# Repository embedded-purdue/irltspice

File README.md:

# IRLTSPICE - An ES@P Project

IRL + LTspice = IRLTSPICE!

IRLTSPICE provides the convenience of spice with the accuracy and testability of a real-life analog circuit.

Simply design your circuit in your EDA tool of choice, or use our handy Python API, upload to the board, and bang!
Your circuit now exists in real life, and you can now do whatever you want!

Run FRAs, send audio through it, use it as a testbed, or whatever else you can imagine.
It's now just an analog circuit.

Analog protyping has never been this easy.

## How it works

The IRLTSPICE board features a bank of resistors, capacitors, and op-amps, so every virtual component has a physical counterpart that was already on the board.

These physical components are then connected to each other via specialized switches, such that the nets are the same as in your virtual design.

## About

IRLTSPICE began as a Purdue Electrical and Computer Engineering senior design project, and is now an Embedded Systems at Purdue (ES@P) project.

## Project Structure
The senior design project uses a monorepo architecture with the following sub-directories:
- `hardware/` Hardware schematics
- `firmware/` Microcontroller firmware
- `software/` On-PC software
- `evilware/` Evil Circuits and Code

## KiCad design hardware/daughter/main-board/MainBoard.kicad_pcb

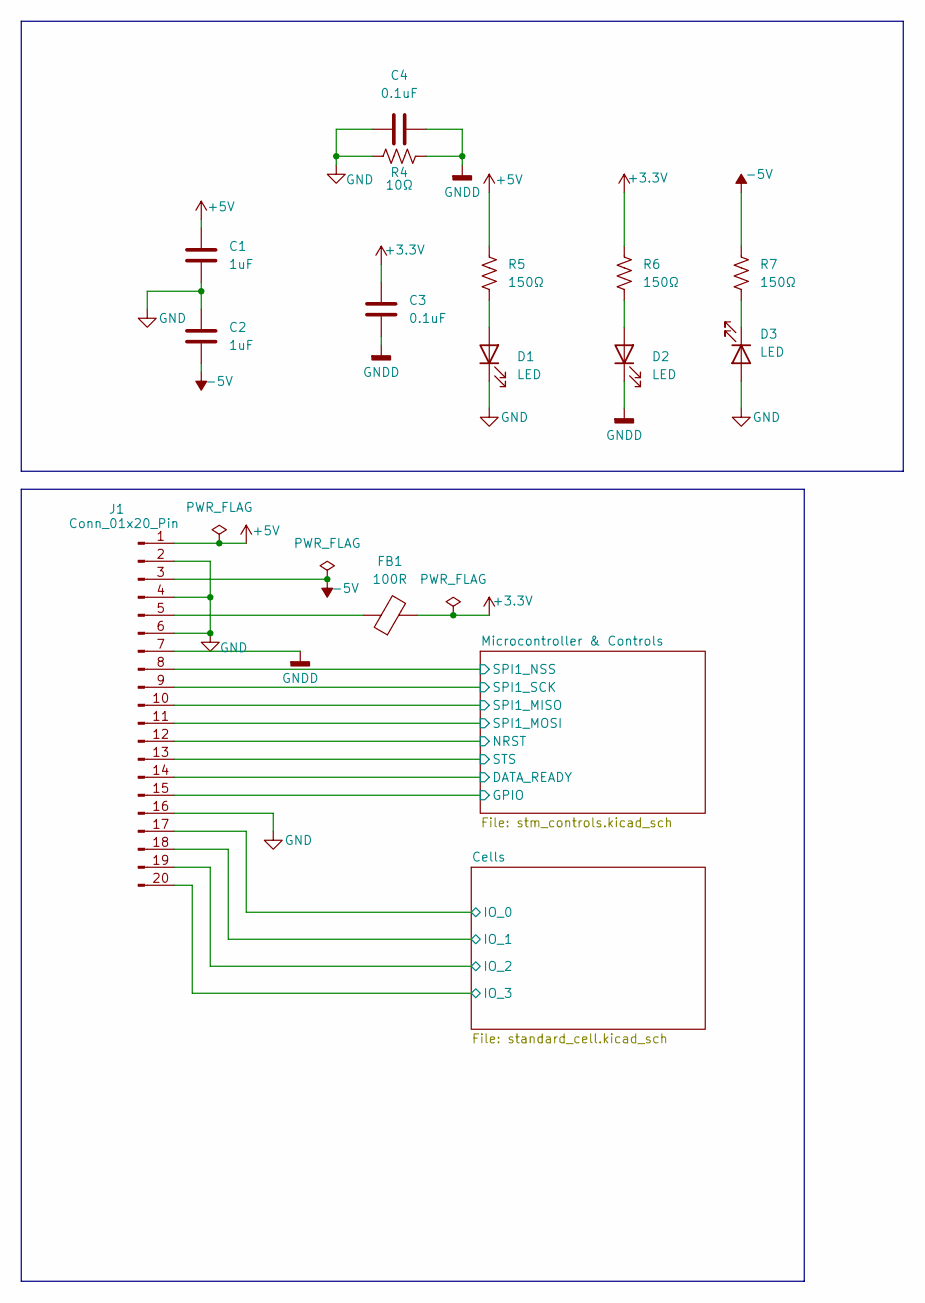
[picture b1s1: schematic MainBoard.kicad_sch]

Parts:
C1, C2: 1uF; C_0603_1608Metric_Pad1.08x0.95mm_HandSolder
C3, C4: 0.1uF; C_0603_1608Metric_Pad1.08x0.95mm_HandSolder
D1, D2, D3: LED; D_0805_2012Metric_Pad1.15x1.40mm_HandSolder
FB1: 100R; R_0603_1608Metric_Pad0.98x0.95mm_HandSolder
J1: Conn_01x20_Pin; PinHeader_2x10_P2.54mm_Horizontal
R4: 10Ω; R_0805_2012Metric_Pad1.20x1.40mm_HandSolder
R5, R6, R7: 150Ω; R_0603_1608Metric_Pad0.98x0.95mm_HandSolder

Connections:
+3.3V: C3.2, FB1.2, R6.1; also elsewhere on the board
+5V: C1.2, J1.1, R5.1; also elsewhere on the board
-5V: C2.1, J1.3, R7.1; also elsewhere on the board
/Cells/IO_0: J1.17; also elsewhere on the board
/Cells/IO_1: J1.18; also elsewhere on the board
/Cells/IO_2: J1.19; also elsewhere on the board
/Cells/IO_3: J1.20; also elsewhere on the board
/Microcontroller & Controls/DATA_READY: J1.14; also elsewhere on the board
/Microcontroller & Controls/GPIO: J1.15; also elsewhere on the board
/Microcontroller & Controls/NRST: J1.12; also elsewhere on the board
/Microcontroller & Controls/SPI1_MISO: J1.10; also elsewhere on the board
/Microcontroller & Controls/SPI1_MOSI: J1.11; also elsewhere on the board
/Microcontroller & Controls/SPI1_NSS: J1.8; also elsewhere on the board
/Microcontroller & Controls/SPI1_SCK: J1.9; also elsewhere on the board
/Microcontroller & Controls/STS: J1.13; also elsewhere on the board
GND: C1.1, C2.2, C4.1, D1.1 (K), D3.2 (A), J1.2, J1.4, J1.6, J1.16, R4.1; also elsewhere on the board
GNDD: C3.1, C4.2, D2.1 (K), J1.7, R4.2; also elsewhere on the board
unnamed: D1.2 (A), R5.2
unnamed: D2.2 (A), R6.2
unnamed: D3.1 (K), R7.2
unnamed: FB1.1, J1.5

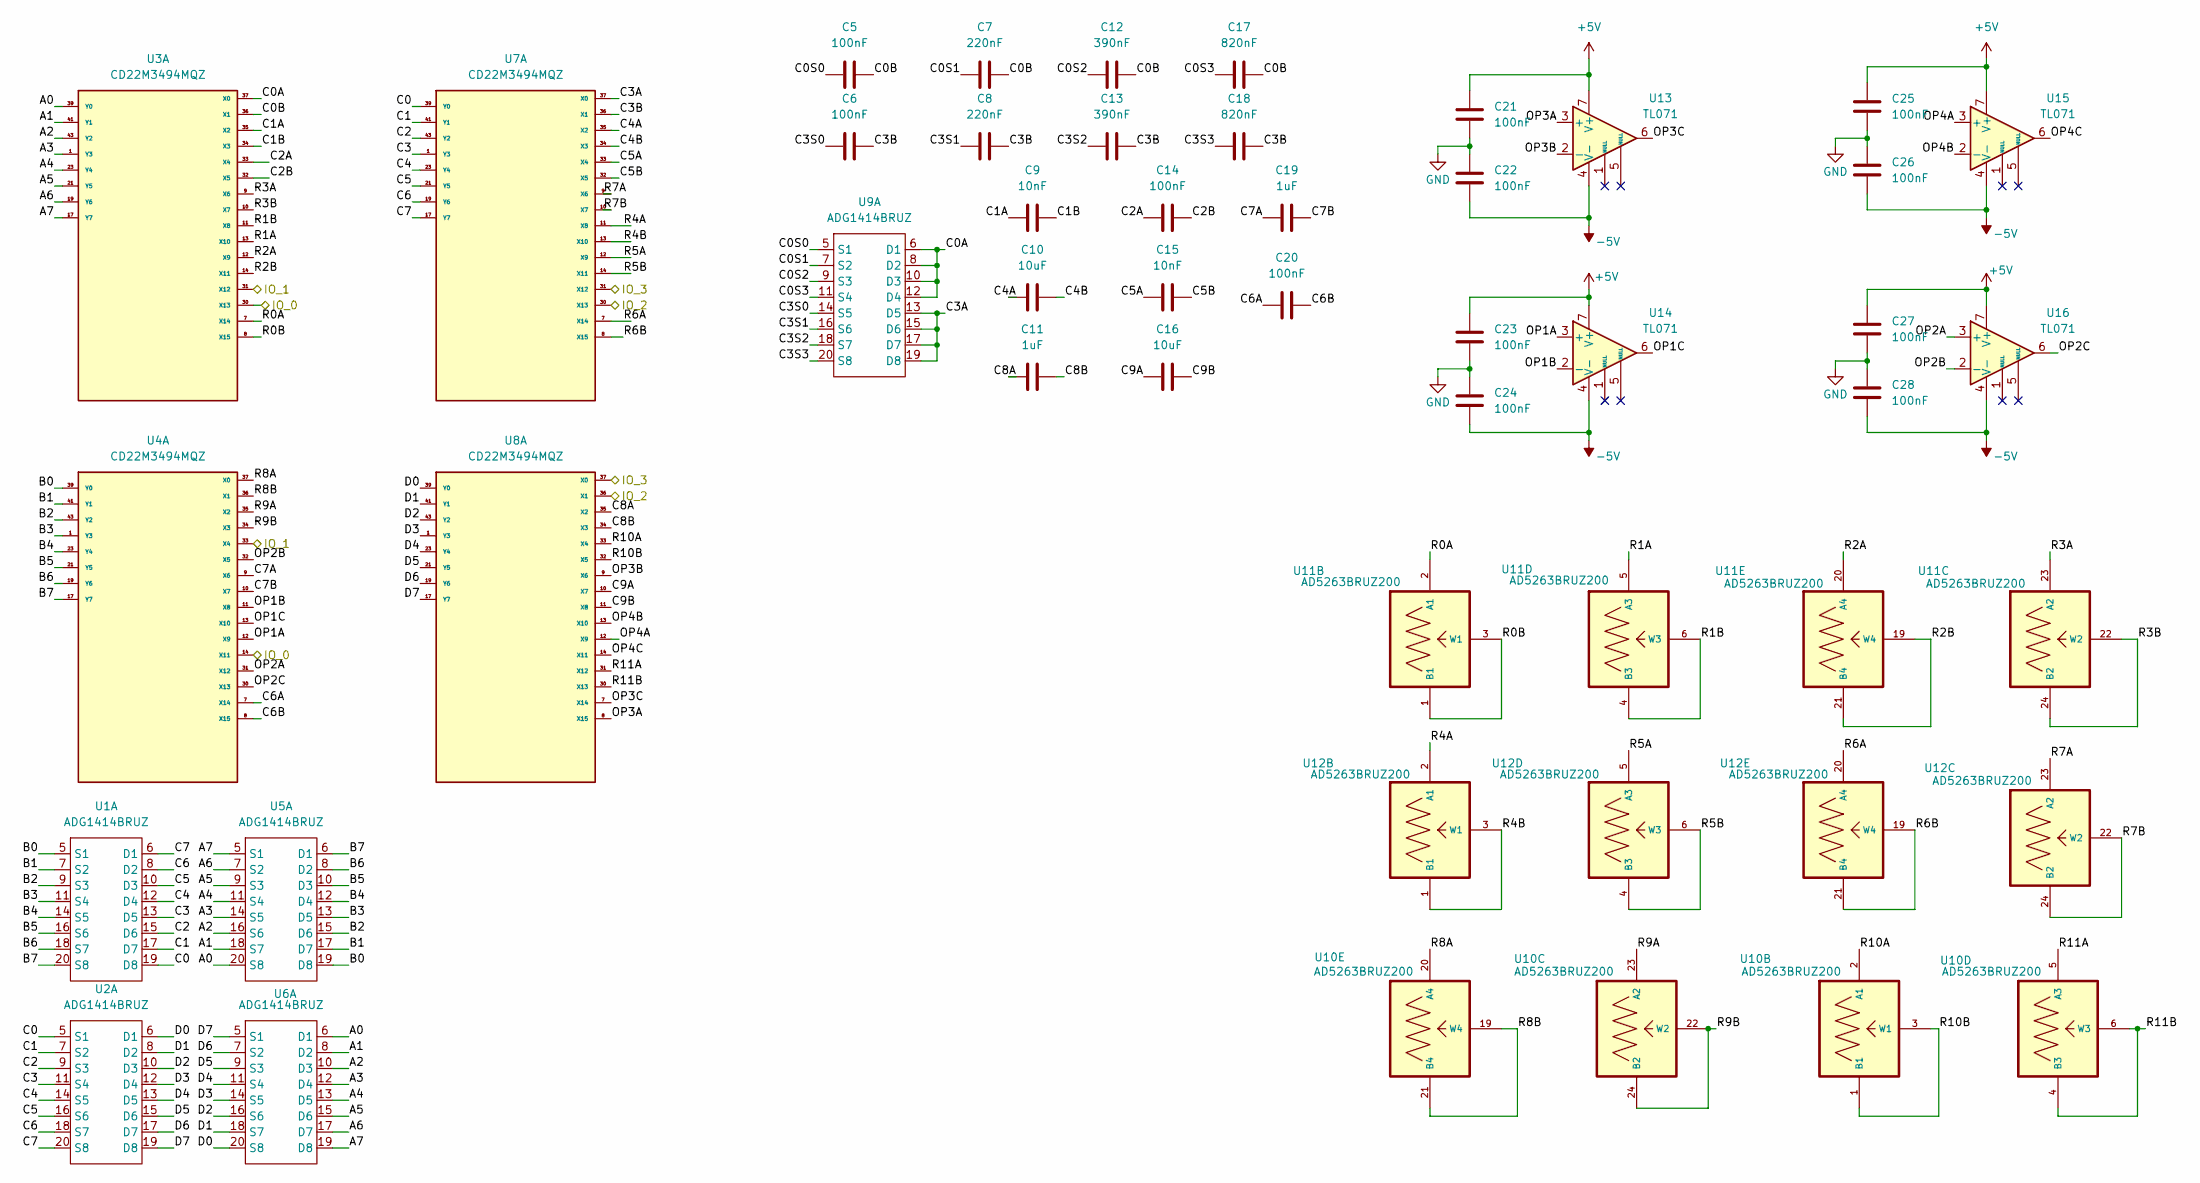
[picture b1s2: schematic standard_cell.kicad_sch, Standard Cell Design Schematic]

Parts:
C5, C6, C14, C20, C21, C22, C23, C24, C25, C26, C27, C28: 100nF; C_0603_1608Metric_Pad1.08x0.95mm_HandSolder
C7, C8: 220nF; C_0603_1608Metric_Pad1.08x0.95mm_HandSolder
C9, C15: 10nF; C_0603_1608Metric_Pad1.08x0.95mm_HandSolder
C10, C16: 10uF; C_0805_2012Metric_Pad1.18x1.45mm_HandSolder
C11, C19: 1uF; C_0603_1608Metric_Pad1.08x0.95mm_HandSolder
C12, C13: 390nF; C_0603_1608Metric_Pad1.08x0.95mm_HandSolder
C17, C18: 820nF; C_0603_1608Metric_Pad1.08x0.95mm_HandSolder
U1, U2, U5, U6, U9: ADG1414BRUZ; HTSSOP-24-1EP_4.4x7.8mm_P0.65mm_EP3.2x5mm
U3, U4, U7, U8: CD22M3494MQZ; PLCC44_16P66X16P66_INR-M; PARTREV September 2011
U10, U11, U12: AD5263BRUZ200; SOP65P640X120-24N; MPN AD5263BRUZ200
U13, U14, U15, U16: TL071; SOIC-8-1EP_3.9x4.9mm_P1.27mm_EP2.29x3mm

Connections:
+5V: C21.1, C23.1, C25.1, C27.1, U13.7 (V+), U14.7 (V+), U15.7 (V+), U16.7 (V+); also elsewhere on the board
-5V: C22.2, C24.2, C26.2, C28.2, U13.4 (V-), U14.4 (V-), U15.4 (V-), U16.4 (V-); also elsewhere on the board
/Cells/A0: U3.39 (Y0), U5.20 (S8), U6.6 (D1)
/Cells/A1: U3.41 (Y1), U5.18 (S7), U6.8 (D2)
/Cells/A2: U3.43 (Y2), U5.16 (S6), U6.10 (D3)
/Cells/A3: U3.1 (Y3), U5.14 (S5), U6.12 (D4)
/Cells/A4: U3.23 (Y4), U5.11 (S4), U6.13 (D5)
/Cells/A5: U3.21 (Y5), U5.9 (S3), U6.15 (D6)
/Cells/A6: U3.19 (Y6), U5.7 (S2), U6.17 (D7)
/Cells/A7: U3.17 (Y7), U5.5 (S1), U6.19 (D8)
/Cells/B0: U1.5 (S1), U4.39 (Y0), U5.19 (D8)
/Cells/B1: U1.7 (S2), U4.41 (Y1), U5.17 (D7)
/Cells/B2: U1.9 (S3), U4.43 (Y2), U5.15 (D6)
/Cells/B3: U1.11 (S4), U4.1 (Y3), U5.13 (D5)
/Cells/B4: U1.14 (S5), U4.23 (Y4), U5.12 (D4)
/Cells/B5: U1.16 (S6), U4.21 (Y5), U5.10 (D3)
/Cells/B6: U1.18 (S7), U4.19 (Y6), U5.8 (D2)
/Cells/B7: U1.20 (S8), U4.17 (Y7), U5.6 (D1)
/Cells/C0: U1.19 (D8), U2.5 (S1), U7.39 (Y0)
/Cells/C0A: U3.37 (X0), U9.6 (D1), U9.8 (D2), U9.10 (D3), U9.12 (D4)
/Cells/C0B: C5.2, C7.2, C12.2, C17.2, U3.36 (X1)
/Cells/C0S0: C5.1, U9.5 (S1)
/Cells/C0S1: C7.1, U9.7 (S2)
/Cells/C0S2: C12.1, U9.9 (S3)
/Cells/C0S3: C17.1, U9.11 (S4)
/Cells/C1: U1.17 (D7), U2.7 (S2), U7.41 (Y1)
/Cells/C1A: C9.1, U3.35 (X2)
/Cells/C1B: C9.2, U3.34 (X3)
/Cells/C2: U1.15 (D6), U2.9 (S3), U7.43 (Y2)
/Cells/C2A: C14.1, U3.33 (X4)
/Cells/C2B: C14.2, U3.32 (X5)
/Cells/C3: U1.13 (D5), U2.11 (S4), U7.1 (Y3)
/Cells/C3A: U7.37 (X0), U9.13 (D5), U9.15 (D6), U9.17 (D7), U9.19 (D8)
/Cells/C3B: C6.2, C8.2, C13.2, C18.2, U7.36 (X1)
/Cells/C3S0: C6.1, U9.14 (S5)
/Cells/C3S1: C8.1, U9.16 (S6)
/Cells/C3S2: C13.1, U9.18 (S7)
/Cells/C3S3: C18.1, U9.20 (S8)
/Cells/C4: U1.12 (D4), U2.14 (S5), U7.23 (Y4)
/Cells/C4A: C10.1, U7.35 (X2)
/Cells/C4B: C10.2, U7.34 (X3)
/Cells/C5: U1.10 (D3), U2.16 (S6), U7.21 (Y5)
/Cells/C5A: C15.1, U7.33 (X4)
/Cells/C5B: C15.2, U7.32 (X5)
/Cells/C6: U1.8 (D2), U2.18 (S7), U7.19 (Y6)
/Cells/C6A: C20.1, U4.7 (X14)
/Cells/C6B: C20.2, U4.8 (X15)
/Cells/C7: U1.6 (D1), U2.20 (S8), U7.17 (Y7)
/Cells/C7A: C19.1, U4.9 (X6)
/Cells/C7B: C19.2, U4.10 (X7)
/Cells/C8A: C11.1, U8.35 (X2)
/Cells/C8B: C11.2, U8.34 (X3)
/Cells/C9A: C16.1, U8.10 (X7)
/Cells/C9B: C16.2, U8.11 (X8)
/Cells/D0: U2.6 (D1), U6.20 (S8), U8.39 (Y0)
/Cells/D1: U2.8 (D2), U6.18 (S7), U8.41 (Y1)
/Cells/D2: U2.10 (D3), U6.16 (S6), U8.43 (Y2)
/Cells/D3: U2.12 (D4), U6.14 (S5), U8.1 (Y3)
/Cells/D4: U2.13 (D5), U6.11 (S4), U8.23 (Y4)
/Cells/D5: U2.15 (D6), U6.9 (S3), U8.21 (Y5)
/Cells/D6: U2.17 (D7), U6.7 (S2), U8.19 (Y6)
/Cells/D7: U2.19 (D8), U6.5 (S1), U8.17 (Y7)
/Cells/IO_0: U3.30 (X13), U4.14 (X11); also elsewhere on the board
/Cells/IO_1: U3.31 (X12), U4.33 (X4); also elsewhere on the board
/Cells/IO_2: U7.30 (X13), U8.36 (X1); also elsewhere on the board
/Cells/IO_3: U7.31 (X12), U8.37 (X0); also elsewhere on the board
/Cells/OP1A: U4.12 (X9), U14.3 (+)
/Cells/OP1B: U4.11 (X8), U14.2 (-)
/Cells/OP1C: U4.13 (X10), U14.6
/Cells/OP2A: U4.31 (X12), U16.3 (+)
/Cells/OP2B: U4.32 (X5), U16.2 (-)
/Cells/OP2C: U4.30 (X13), U16.6
/Cells/OP3A: U8.8 (X15), U13.3 (+)
/Cells/OP3B: U8.9 (X6), U13.2 (-)
/Cells/OP3C: U8.7 (X14), U13.6
/Cells/OP4A: U8.12 (X9), U15.3 (+)
/Cells/OP4B: U8.13 (X10), U15.2 (-)
/Cells/OP4C: U8.14 (X11), U15.6
/Cells/R0A: U3.7 (X14), U11.2 (A1)
/Cells/R0B: U3.8 (X15), U11.1 (B1), U11.3 (W1)
/Cells/R1A: U3.13 (X10), U11.5 (A3)
/Cells/R1B: U3.11 (X8), U11.4 (B3), U11.6 (W3)
/Cells/R2A: U3.12 (X9), U11.20 (A4)
/Cells/R2B: U3.14 (X11), U11.19 (W4), U11.21 (B4)
/Cells/R3A: U3.9 (X6), U11.23 (A2)
/Cells/R3B: U3.10 (X7), U11.22 (W2), U11.24 (B2)
/Cells/R4A: U7.11 (X8), U12.2 (A1)
/Cells/R4B: U7.13 (X10), U12.1 (B1), U12.3 (W1)
/Cells/R5A: U7.12 (X9), U12.5 (A3)
/Cells/R5B: U7.14 (X11), U12.4 (B3), U12.6 (W3)
/Cells/R6A: U7.7 (X14), U12.20 (A4)
/Cells/R6B: U7.8 (X15), U12.19 (W4), U12.21 (B4)
/Cells/R7A: U7.9 (X6), U12.23 (A2)
/Cells/R7B: U7.10 (X7), U12.22 (W2), U12.24 (B2)
/Cells/R8A: U4.37 (X0), U10.20 (A4)
/Cells/R8B: U4.36 (X1), U10.19 (W4), U10.21 (B4)
/Cells/R9A: U4.35 (X2), U10.23 (A2)
/Cells/R9B: U4.34 (X3), U10.22 (W2), U10.24 (B2)
/Cells/R10A: U8.33 (X4), U10.2 (A1)
/Cells/R10B: U8.32 (X5), U10.1 (B1), U10.3 (W1)
/Cells/R11A: U8.31 (X12), U10.5 (A3)
/Cells/R11B: U8.30 (X13), U10.4 (B3), U10.6 (W3)
GND: C21.2, C22.1, C23.2, C24.1, C25.2, C26.1, C27.2, C28.1; also elsewhere on the board

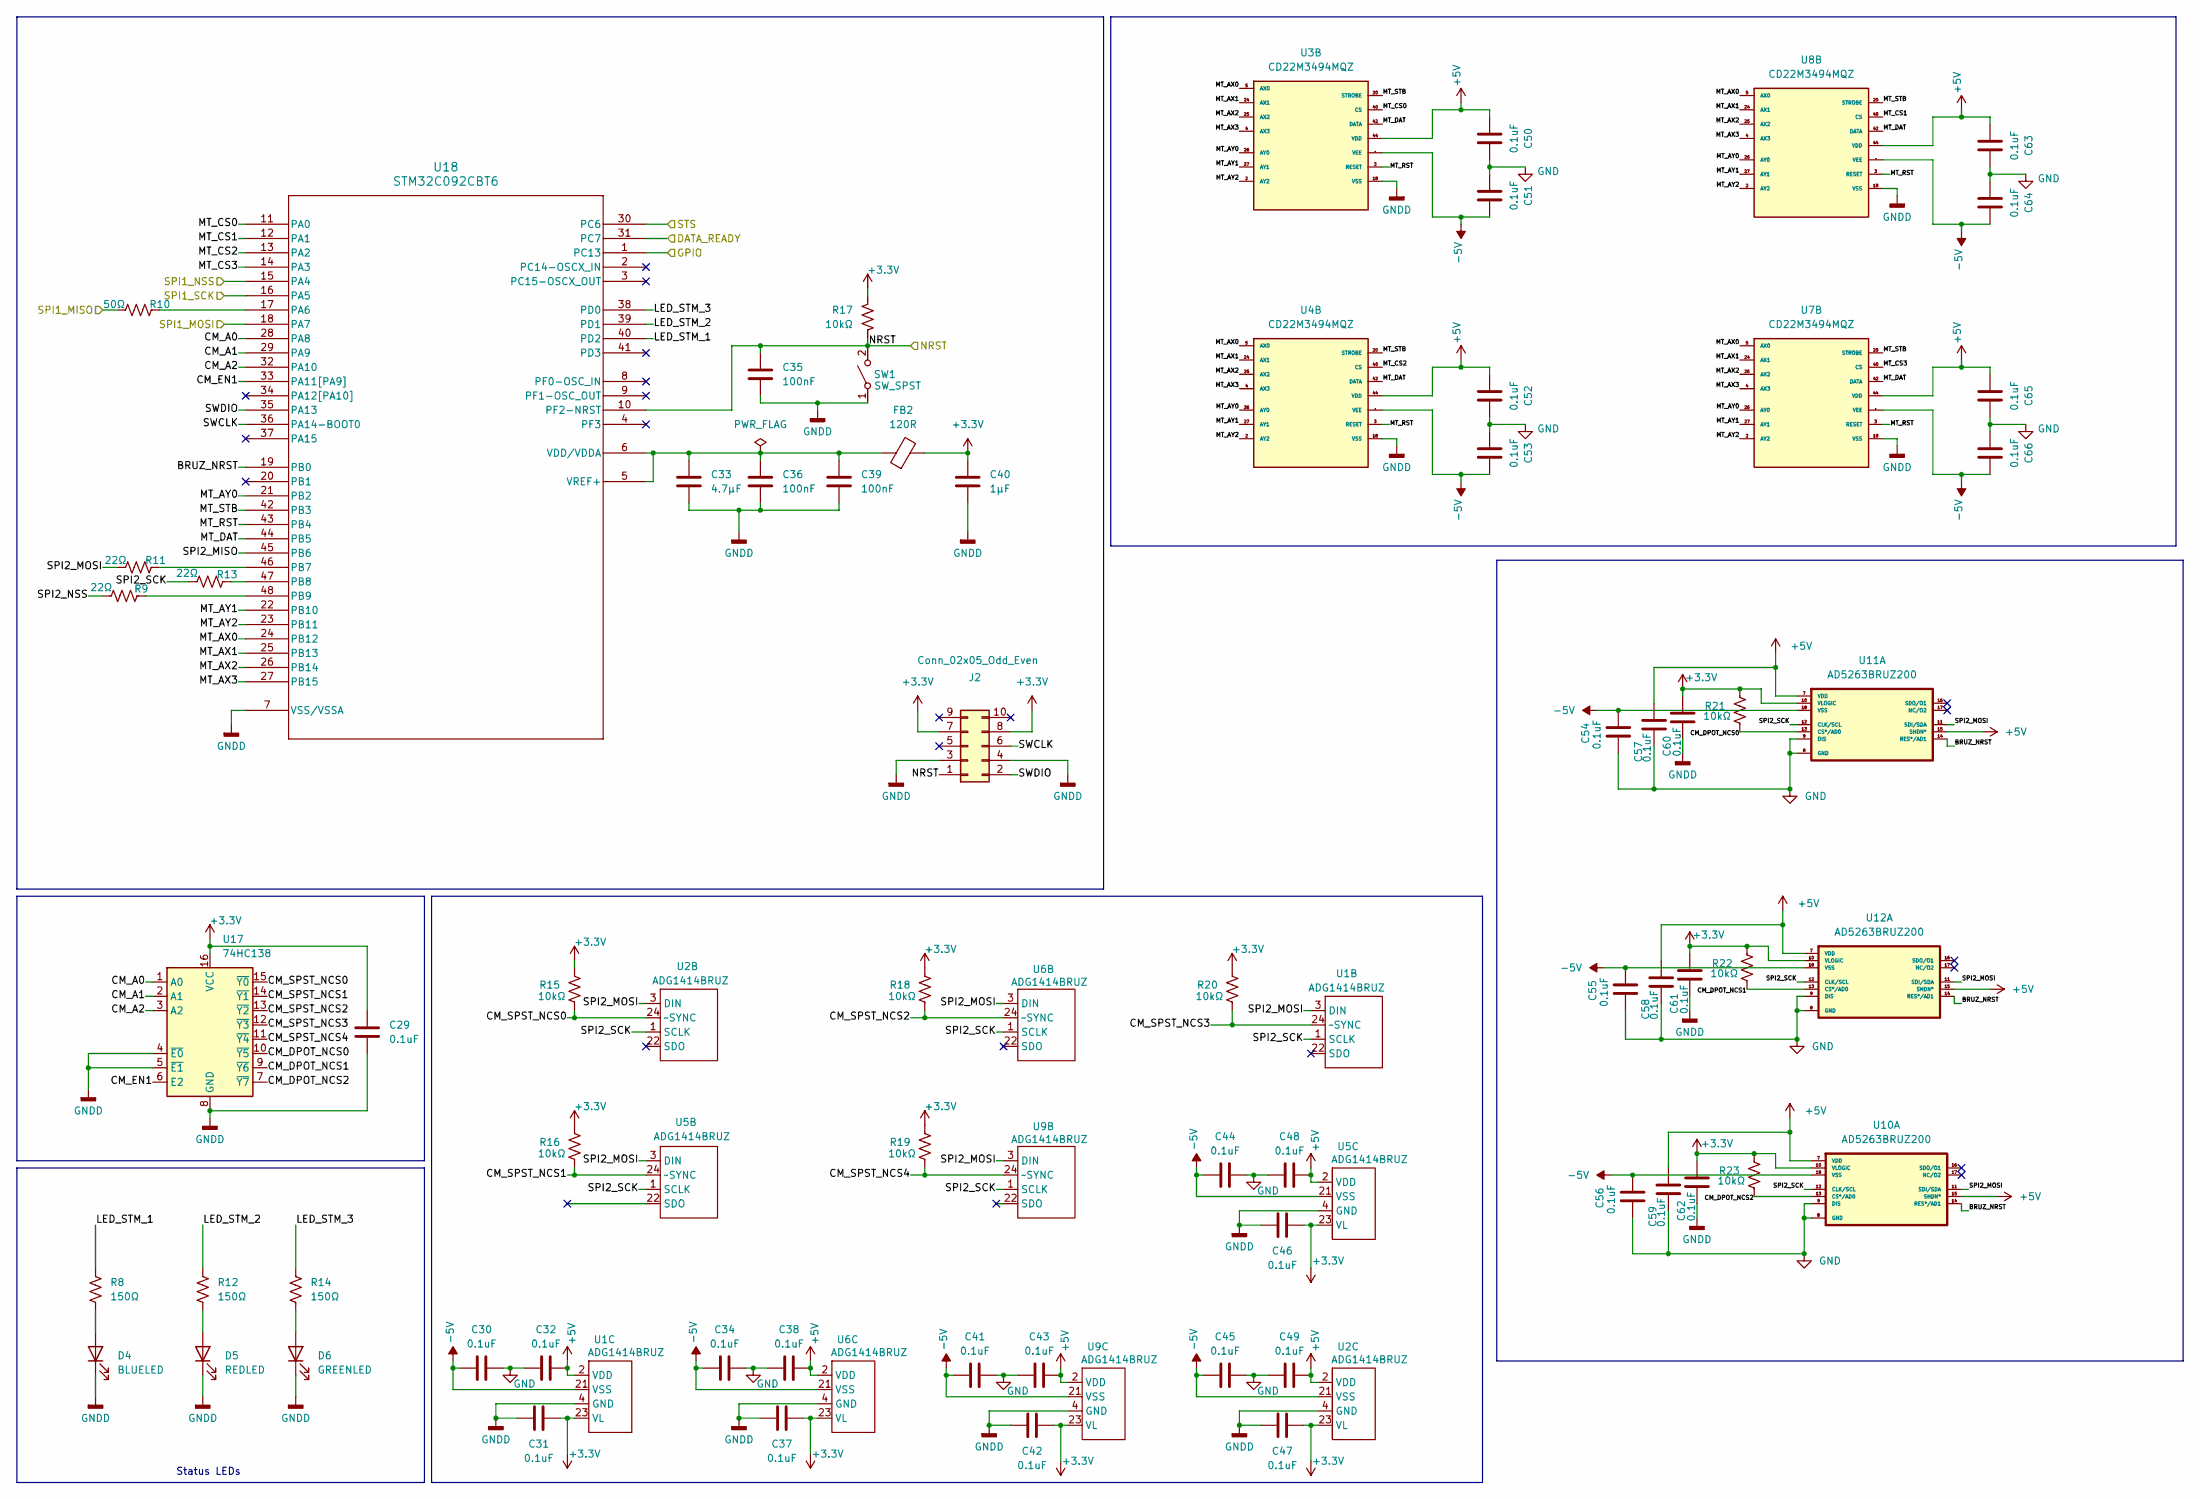
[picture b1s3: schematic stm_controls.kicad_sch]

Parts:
C29, C30, C31, C32, C34, C37, C38, C41, C42, C43, C44, C45, C46, C47, C48, C49, C50, C51, C52, C53, C54, C55, C56, C57, C58, C59, C60, C61, C62, C63, C64, C65, C66: 0.1uF; C_0603_1608Metric_Pad1.08x0.95mm_HandSolder
C33: 4.7µF; C_0603_1608Metric_Pad1.08x0.95mm_HandSolder
C35, C36, C39: 100nF; C_0603_1608Metric_Pad1.08x0.95mm_HandSolder
C40: 1µF; C_0603_1608Metric_Pad1.08x0.95mm_HandSolder
D4: BLUELED; D_0805_2012Metric_Pad1.15x1.40mm_HandSolder
D5: REDLED; D_0805_2012Metric_Pad1.15x1.40mm_HandSolder
D6: GREENLED; D_0805_2012Metric_Pad1.15x1.40mm_HandSolder
FB2: 120R; L_0603_1608Metric_Pad1.05x0.95mm_HandSolder
J2: Conn_02x05_Odd_Even; PinHeader_2x05_P2.54mm_Vertical
R8, R12, R14: 150Ω; R_0603_1608Metric_Pad0.98x0.95mm_HandSolder
R9, R11, R13: 22Ω; R_0603_1608Metric_Pad0.98x0.95mm_HandSolder
R10: 50Ω; R_0603_1608Metric_Pad0.98x0.95mm_HandSolder
R15, R16, R17, R18, R19, R20, R21, R22, R23: 10kΩ; R_0603_1608Metric_Pad0.98x0.95mm_HandSolder
SW1: SW_SPST; SW_SPST_SKQG_WithoutStem
U1, U2, U5, U6, U9: ADG1414BRUZ; HTSSOP-24-1EP_4.4x7.8mm_P0.65mm_EP3.2x5mm
U3, U4, U7, U8: CD22M3494MQZ; PLCC44_16P66X16P66_INR-M; PARTREV September 2011
U10, U11, U12: AD5263BRUZ200; SOP65P640X120-24N
U17: 74HC138; SOIC-16_3.9x9.9mm_P1.27mm
U18: STM32C092CBT6; LQFP48_STM

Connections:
+3.3V: C29.1, C31.1, C37.1, C40.1, C42.1, C46.1, C47.1, C60.1, C61.1, C62.1, FB2.2, J2.7, J2.8, R15.2, R16.2, R17.1, R18.2, R19.2, R20.2, R21.2, R22.2, R23.2, U1.23 (VL), U2.23 (VL), U5.23 (VL), U6.23 (VL), U9.23 (VL), U10.10 (VLOGIC), U11.10 (VLOGIC), U12.10 (VLOGIC), U17.16 (VCC); also elsewhere on the board
+5V: C32.1, C38.1, C43.1, C48.1, C49.1, C50.1, C52.1, C57.1, C58.1, C59.1, C63.1, C65.1, U1.2 (VDD), U2.2 (VDD), U3.44 (VDD), U4.44 (VDD), U5.2 (VDD), U6.2 (VDD), U7.44 (VDD), U8.44 (VDD), U9.2 (VDD), U10.7 (VDD), U10.15 (SHDN*), U11.7 (VDD), U11.15 (SHDN*), U12.7 (VDD), U12.15 (SHDN*); also elsewhere on the board
-5V: C30.2, C34.2, C41.2, C44.2, C45.2, C51.2, C53.2, C54.1, C55.1, C56.1, C64.2, C66.2, U1.21 (VSS), U2.21 (VSS), U3.22 (VEE), U4.22 (VEE), U5.21 (VSS), U6.21 (VSS), U7.22 (VEE), U8.22 (VEE), U9.21 (VSS), U10.18 (VSS), U11.18 (VSS), U12.18 (VSS); also elsewhere on the board
/Microcontroller & Controls/BRUZ_NRST: U10.14 (RES*/AD1), U11.14 (RES*/AD1), U12.14 (RES*/AD1), U18.19 (PB0)
/Microcontroller & Controls/CM_A0: U17.1 (A0), U18.28 (PA8)
/Microcontroller & Controls/CM_A1: U17.2 (A1), U18.29 (PA9)
/Microcontroller & Controls/CM_A2: U17.3 (A2), U18.32 (PA10)
/Microcontroller & Controls/CM_DPOT_NCS0: R21.1, U11.13 (CS*/AD0), U17.10 (~Y5)
/Microcontroller & Controls/CM_DPOT_NCS1: R22.1, U12.13 (CS*/AD0), U17.9 (~Y6)
/Microcontroller & Controls/CM_DPOT_NCS2: R23.1, U10.13 (CS*/AD0), U17.7 (~Y7)
/Microcontroller & Controls/CM_EN1: U17.6 (E2), U18.33 (PA11[PA9])
/Microcontroller & Controls/CM_SPST_NCS0: R15.1, U2.24 (~SYNC), U17.15 (~Y0)
/Microcontroller & Controls/CM_SPST_NCS1: R16.1, U5.24 (~SYNC), U17.14 (~Y1)
/Microcontroller & Controls/CM_SPST_NCS2: R18.1, U6.24 (~SYNC), U17.13 (~Y2)
/Microcontroller & Controls/CM_SPST_NCS3: R20.1, U1.24 (~SYNC), U17.12 (~Y3)
/Microcontroller & Controls/CM_SPST_NCS4: R19.1, U9.24 (~SYNC), U17.11 (~Y4)
/Microcontroller & Controls/DATA_READY: U18.31 (PC7); also elsewhere on the board
/Microcontroller & Controls/GPIO: U18.1 (PC13); also elsewhere on the board
/Microcontroller & Controls/LED_STM_1: R8.1, U18.40 (PD2)
/Microcontroller & Controls/LED_STM_2: R12.1, U18.39 (PD1)
/Microcontroller & Controls/LED_STM_3: R14.1, U18.38 (PD0)
/Microcontroller & Controls/MT_AX0: U3.5 (AX0), U4.5 (AX0), U7.5 (AX0), U8.5 (AX0), U18.24 (PB12)
/Microcontroller & Controls/MT_AX1: U3.24 (AX1), U4.24 (AX1), U7.24 (AX1), U8.24 (AX1), U18.25 (PB13)
/Microcontroller & Controls/MT_AX2: U3.25 (AX2), U4.25 (AX2), U7.25 (AX2), U8.25 (AX2), U18.26 (PB14)
/Microcontroller & Controls/MT_AX3: U3.4 (AX3), U4.4 (AX3), U7.4 (AX3), U8.4 (AX3), U18.27 (PB15)
/Microcontroller & Controls/MT_AY0: U3.26 (AY0), U4.26 (AY0), U7.26 (AY0), U8.26 (AY0), U18.21 (PB2)
/Microcontroller & Controls/MT_AY1: U3.27 (AY1), U4.27 (AY1), U7.27 (AY1), U8.27 (AY1), U18.22 (PB10)
/Microcontroller & Controls/MT_AY2: U3.2 (AY2), U4.2 (AY2), U7.2 (AY2), U8.2 (AY2), U18.23 (PB11)
/Microcontroller & Controls/MT_CS0: U3.40 (CS), U18.11 (PA0)
/Microcontroller & Controls/MT_CS1: U8.40 (CS), U18.12 (PA1)
/Microcontroller & Controls/MT_CS2: U4.40 (CS), U18.13 (PA2)
/Microcontroller & Controls/MT_CS3: U7.40 (CS), U18.14 (PA3)
/Microcontroller & Controls/MT_DAT: U3.42 (DATA), U4.42 (DATA), U7.42 (DATA), U8.42 (DATA), U18.44 (PB5)
/Microcontroller & Controls/MT_RST: U3.3 (RESET), U4.3 (RESET), U7.3 (RESET), U8.3 (RESET), U18.43 (PB4)
/Microcontroller & Controls/MT_STB: U3.20 (STROBE), U4.20 (STROBE), U7.20 (STROBE), U8.20 (STROBE), U18.42 (PB3)
/Microcontroller & Controls/NRST: C35.1, J2.1, R17.2, SW1.2 (B), U18.10 (PF2-NRST); also elsewhere on the board
/Microcontroller & Controls/SPI1_MISO: R10.1; also elsewhere on the board
/Microcontroller & Controls/SPI1_MOSI: U18.18 (PA7); also elsewhere on the board
/Microcontroller & Controls/SPI1_NSS: U18.15 (PA4); also elsewhere on the board
/Microcontroller & Controls/SPI1_SCK: U18.16 (PA5); also elsewhere on the board
/Microcontroller & Controls/SPI2_MISO: U18.45 (PB6)
/Microcontroller & Controls/SPI2_MOSI: R11.1, U1.3 (DIN), U2.3 (DIN), U5.3 (DIN), U6.3 (DIN), U9.3 (DIN), U10.11 (SDI/SDA), U11.11 (SDI/SDA), U12.11 (SDI/SDA)
/Microcontroller & Controls/SPI2_NSS: R9.1
/Microcontroller & Controls/SPI2_SCK: R13.1, U1.1 (SCLK), U2.1 (SCLK), U5.1 (SCLK), U6.1 (SCLK), U9.1 (SCLK), U10.12 (CLK/SCL), U11.12 (CLK/SCL), U12.12 (CLK/SCL)
/Microcontroller & Controls/STS: U18.30 (PC6); also elsewhere on the board
/Microcontroller & Controls/SWCLK: J2.6, U18.36 (PA14-BOOT0)
/Microcontroller & Controls/SWDIO: J2.2, U18.35 (PA13)
GND: C30.1, C32.2, C34.1, C38.2, C41.1, C43.2, C44.1, C45.1, C48.2, C49.2, C50.2, C51.1, C52.2, C53.1, C54.2, C55.2, C56.2, C57.2, C58.2, C59.2, C63.2, C64.1, C65.2, C66.1, U10.8 (GND), U10.9 (DIS), U11.8 (GND), U11.9 (DIS), U12.8 (GND), U12.9 (DIS); also elsewhere on the board
GNDD: C29.2, C31.2, C33.2, C35.2, C36.2, C37.2, C39.2, C40.2, C42.2, C46.2, C47.2, C60.2, C61.2, C62.2, D4.1 (K), D5.1 (K), D6.1 (K), J2.3, J2.4, SW1.1 (A), U1.4 (GND), U2.4 (GND), U3.18 (VSS), U4.18 (VSS), U5.4 (GND), U6.4 (GND), U7.18 (VSS), U8.18 (VSS), U9.4 (GND), U17.4 (~E0), U17.5 (~E1), U17.8 (GND), U18.7 (VSS/VSSA); also elsewhere on the board
unnamed: D4.2 (A), R8.2
unnamed: D5.2 (A), R12.2
unnamed: D6.2 (A), R14.2
unnamed: R10.2, U18.17 (PA6)
unnamed: R11.2, U18.46 (PB7)
unnamed: R13.2, U18.47 (PB8)
unnamed: R9.2, U18.48 (PB9)
unnamed: C33.1, C36.1, C39.1, FB2.1, U18.5 (VREF+), U18.6 (VDD/VDDA)

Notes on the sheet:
Status LEDs

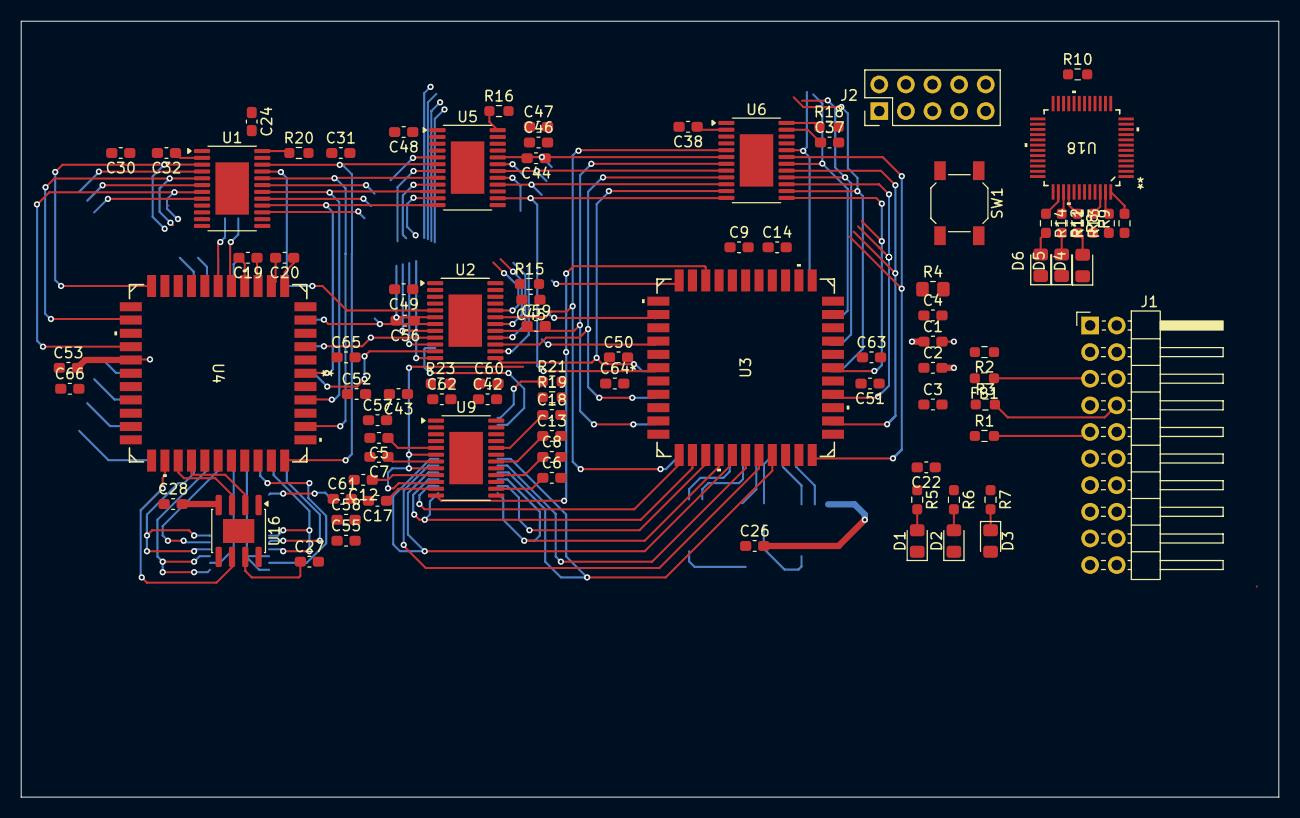
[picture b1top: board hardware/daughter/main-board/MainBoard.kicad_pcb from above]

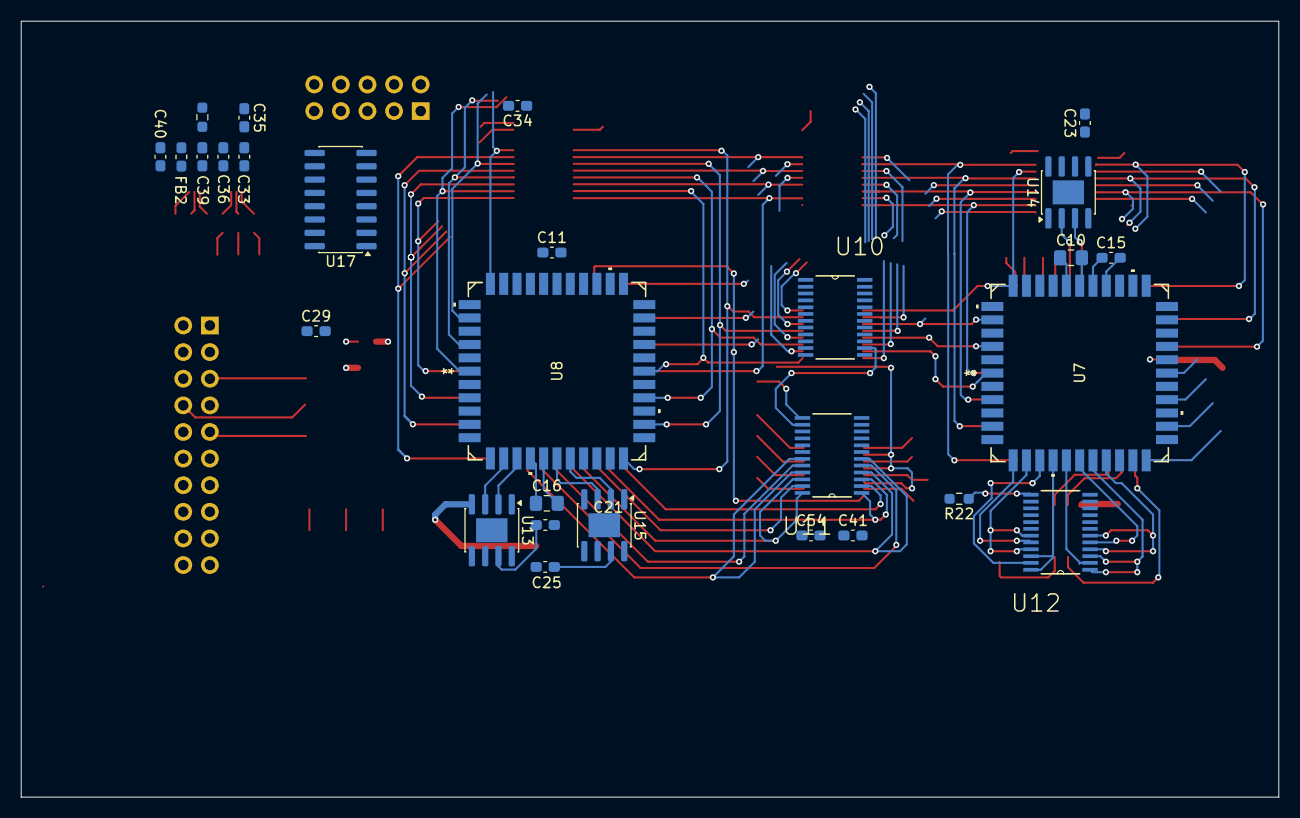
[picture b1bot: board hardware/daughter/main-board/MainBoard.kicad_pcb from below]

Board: 4 copper layers, 120.0 x 74.0 mm, 118 parts (28 on the bottom side), 159 nets.

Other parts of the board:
R1, R2, R3: 50Ω; R_0603_1608Metric_Pad0.98x0.95mm_HandSolder

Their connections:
/Microcontroller & Controls/SPI1_MOSI: R2.2; also elsewhere on the board
/Microcontroller & Controls/SPI1_NSS: R3.2; also elsewhere on the board
/Microcontroller & Controls/SPI1_SCK: R1.2; also elsewhere on the board

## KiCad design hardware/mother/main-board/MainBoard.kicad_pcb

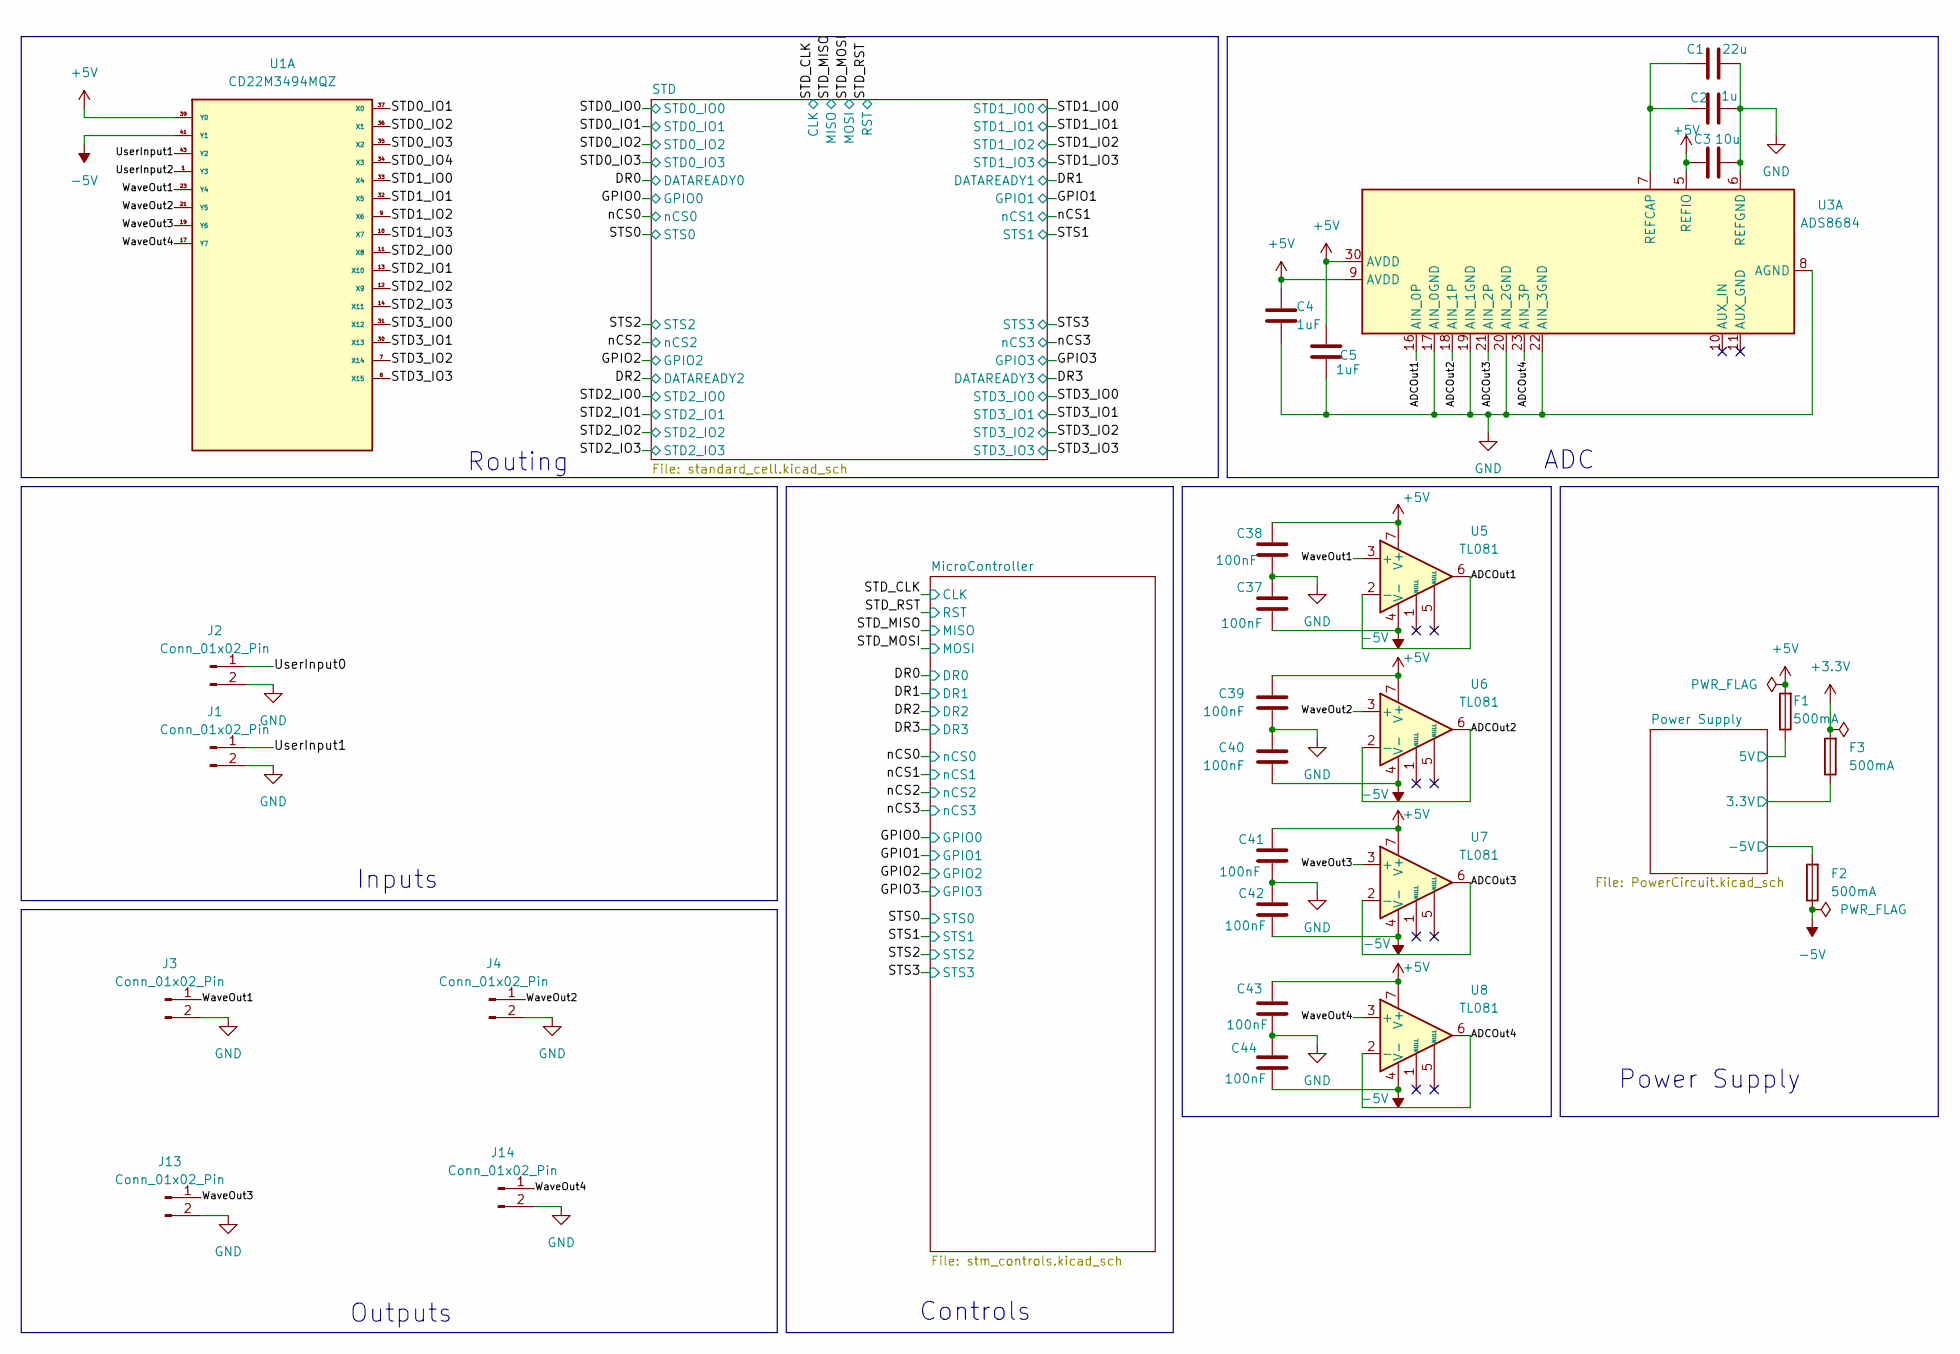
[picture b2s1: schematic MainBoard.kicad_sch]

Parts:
C1: 22u; C_0603_1608Metric_Pad1.08x0.95mm_HandSolder
C2: 1u; C_0603_1608Metric_Pad1.08x0.95mm_HandSolder
C3: 10u; C_0603_1608Metric_Pad1.08x0.95mm_HandSolder
C4, C5: 1uF; C_0603_1608Metric_Pad1.08x0.95mm_HandSolder
C37, C38, C39, C40, C41, C42, C43, C44: 100nF; C_0603_1608Metric_Pad1.08x0.95mm_HandSolder
F1, F2, F3: 500mA; Fuse_0603_1608Metric_Pad1.05x0.95mm_HandSolder
J1, J2, J3, J4, J13, J14: Conn_01x02_Pin; PinHeader_1x02_P2.54mm_Vertical
U1: CD22M3494MQZ; PLCC44_16P66X16P66_INR-M; PARTREV September 2011
U3: ADS8684; TSSOP-38_4.4x9.7mm_P0.5mm
U5, U6, U7, U8: TL081; SOIC-8-1EP_3.9x4.9mm_P1.27mm_EP2.29x3mm

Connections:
+3.3V: F3.2; also elsewhere on the board
+5V: C3.1, C4.1, C5.1, C38.1, C39.1, C41.1, C43.1, F1.2, U1.39 (Y0), U3.5 (REFIO), U3.9 (AVDD), U3.30 (AVDD), U5.7 (V+), U6.7 (V+), U7.7 (V+), U8.7 (V+); also elsewhere on the board
-5V: C37.2, C40.2, C42.2, C44.2, F2.1, U1.41 (Y1), U5.4 (V-), U6.4 (V-), U7.4 (V-), U8.4 (V-); also elsewhere on the board
/ADCOut1: U3.16 (AIN_0P), U5.2 (-), U5.6
/ADCOut2: U3.18 (AIN_1P), U6.2 (-), U6.6
/ADCOut3: U3.21 (AIN_2P), U7.2 (-), U7.6
/ADCOut4: U3.23 (AIN_3P), U8.2 (-), U8.6
/Power Supply/3.3V_STATUS: F3.1; also elsewhere on the board
/Power Supply/5V_STATUS: F1.1; also elsewhere on the board
/Power Supply/-5V_STATUS: F2.2; also elsewhere on the board
/STD0_IO1: U1.37 (X0); also elsewhere on the board
/STD0_IO2: U1.36 (X1); also elsewhere on the board
/STD0_IO3: U1.35 (X2); also elsewhere on the board
/STD0_IO4: U1.34 (X3)
/STD1_IO0: U1.33 (X4); also elsewhere on the board
/STD1_IO1: U1.32 (X5); also elsewhere on the board
/STD1_IO2: U1.9 (X6); also elsewhere on the board
/STD1_IO3: U1.10 (X7); also elsewhere on the board
/STD2_IO0: U1.11 (X8); also elsewhere on the board
/STD2_IO1: U1.13 (X10); also elsewhere on the board
/STD2_IO2: U1.12 (X9); also elsewhere on the board
/STD2_IO3: U1.14 (X11); also elsewhere on the board
/STD3_IO0: U1.31 (X12); also elsewhere on the board
/STD3_IO1: U1.30 (X13); also elsewhere on the board
/STD3_IO2: U1.7 (X14); also elsewhere on the board
/STD3_IO3: U1.8 (X15); also elsewhere on the board
/UserInput0: J2.1
/UserInput1: J1.1, U1.43 (Y2)
/UserInput2: U1.1 (Y3)
/WaveOut1: J3.1, U1.23 (Y4), U5.3 (+)
/WaveOut2: J4.1, U1.21 (Y5), U6.3 (+)
/WaveOut3: J13.1, U1.19 (Y6), U7.3 (+)
/WaveOut4: J14.1, U1.17 (Y7), U8.3 (+)
GND: C1.2, C2.2, C3.2, C4.2, C5.2, C37.1, C38.2, C39.2, C40.1, C41.2, C42.1, C43.2, C44.1, J1.2, J2.2, J3.2, J4.2, J13.2, J14.2, U3.6 (REFGND), U3.8 (AGND), U3.17 (AIN_0GND), U3.19 (AIN_1GND), U3.20 (AIN_2GND), U3.22 (AIN_3GND); also elsewhere on the board
unnamed: U3.28 (AGND), U3.29 (AGND), U3.31 (AGND), U3.32 (AGND)
unnamed: C1.1, C2.1, U3.7 (REFCAP)

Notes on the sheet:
Inputs
Controls
Outputs
Power Supply
Routing
ADC
